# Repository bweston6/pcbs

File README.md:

# PCBs
## PiKVM
The [PiPVM](https://github.com/pikvm/pikvm) project requires some additional hardware for ATX system control.

This PCB implements the circuit from this section: <https://github.com/pikvm/pikvm#setting-up-the-v2> in a Raspberry Pi uHat footprint, per the specification at <https://github.com/raspberrypi/hats>.

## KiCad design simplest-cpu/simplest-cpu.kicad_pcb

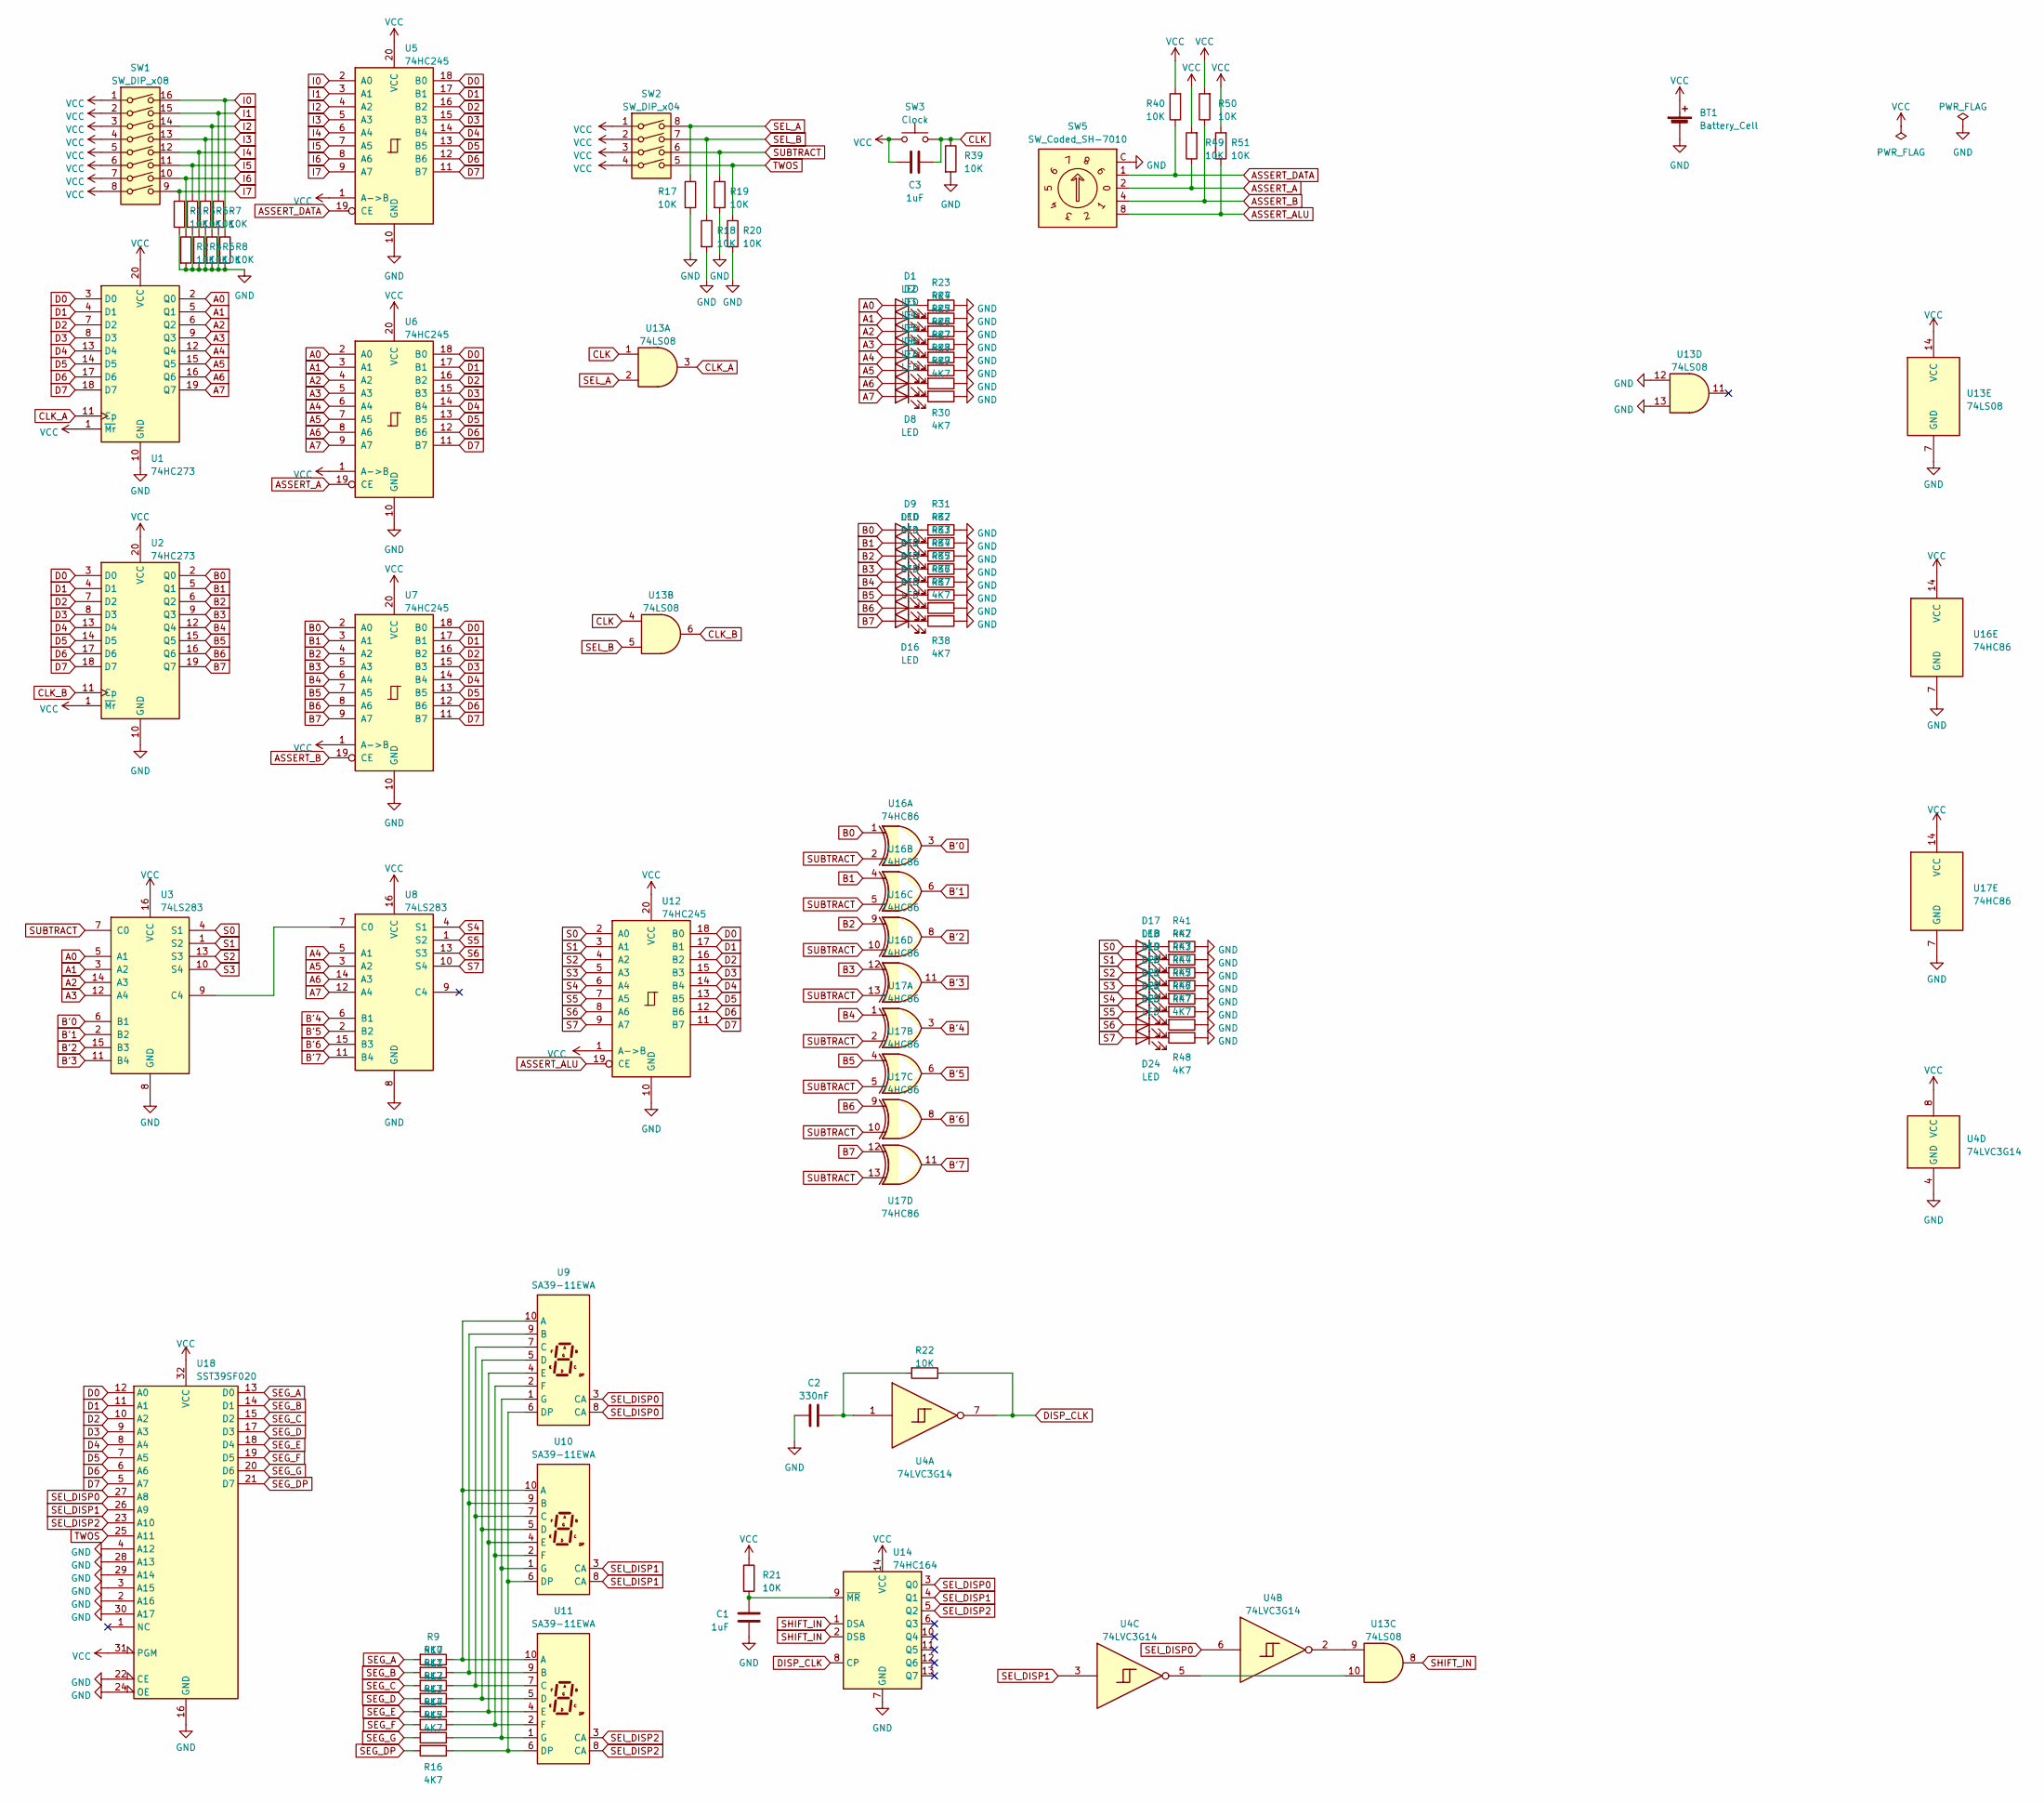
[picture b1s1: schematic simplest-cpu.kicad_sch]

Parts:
BT1: Battery_Cell; BatteryHolder_Keystone_3034_1x20mm
C1, C3: 1uF; C_0805_2012Metric_Pad1.18x1.45mm_HandSolder
C2: 330nF; C_0805_2012Metric_Pad1.18x1.45mm_HandSolder
D1, D2, D3, D4, D5, D6, D7, D8, D9, D10, D11, D12, D13, D14, D15, D16, D17, D18, D19, D20, D21, D22, D23, D24: LED; LED_0805_2012Metric_Pad1.15x1.40mm_HandSolder
R1, R2, R3, R4, R5, R6, R7, R8, R17, R18, R19, R20, R21, R22, R39, R40, R49, R50, R51: 10K; R_0805_2012Metric_Pad1.20x1.40mm_HandSolder
R9, R10, R11, R12, R13, R14, R15, R16, R23, R24, R25, R26, R27, R28, R29, R30, R31, R32, R33, R34, R35, R36, R37, R38, R41, R42, R43, R44, R45, R46, R47, R48: 4K7; R_0805_2012Metric_Pad1.20x1.40mm_HandSolder
SW1: SW_DIP_x08; SW_DIP_SPSTx08_Slide_6.7x21.88mm_W7.62mm_P2.54mm_LowProfile
SW2: SW_DIP_x04; SW_DIP_SPSTx04_Slide_6.7x11.72mm_W7.62mm_P2.54mm_LowProfile
SW3: Clock; SW_Cherry_MX_1.00u_PCB
SW5: SW_Coded_SH-7010; Nidec_Copal_SH-7010C
U1, U2: 74HC273; TSSOP-20_4.4x6.5mm_P0.65mm
U3, U8: 74LS283; DIP-16_W7.62mm
U4: 74LVC3G14; SSOP-8_2.95x2.8mm_P0.65mm
U5, U6, U7, U12: 74HC245; TSSOP-20_4.4x6.5mm_P0.65mm
U9, U10, U11: SA39-11EWA; Sx39-1xxxxx
U13: 74LS08; TSSOP-14_4.4x5mm_P0.65mm
U14: 74HC164; TSSOP-14_4.4x5mm_P0.65mm
U16, U17: 74HC86; TSSOP-14_4.4x5mm_P0.65mm
U18: SST39SF020; PLCC-32_THT-Socket

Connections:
A0: D1.2 (A), U1.2 (Q0), U3.5 (A1), U6.2 (A0)
A1: D2.2 (A), U1.5 (Q1), U3.3 (A2), U6.3 (A1)
A2: D3.2 (A), U1.6 (Q2), U3.14 (A3), U6.4 (A2)
A3: D4.2 (A), U1.9 (Q3), U3.12 (A4), U6.5 (A3)
A4: D5.2 (A), U1.12 (Q4), U6.6 (A4), U8.5 (A1)
A5: D6.2 (A), U1.15 (Q5), U6.7 (A5), U8.3 (A2)
A6: D7.2 (A), U1.16 (Q6), U6.8 (A6), U8.14 (A3)
A7: D8.2 (A), U1.19 (Q7), U6.9 (A7), U8.12 (A4)
ASSERT_A: R49.1, SW5.2, U6.19 (CE)
ASSERT_ALU: R51.1, SW5.8, U12.19 (CE)
ASSERT_B: R50.1, SW5.4, U7.19 (CE)
ASSERT_DATA: R40.1, SW5.1, U5.19 (CE)
B0: D9.2 (A), U2.2 (Q0), U7.2 (A0), U16.1
B1: D10.2 (A), U2.5 (Q1), U7.3 (A1), U16.4
B2: D11.2 (A), U2.6 (Q2), U7.4 (A2), U16.9
B3: D12.2 (A), U2.9 (Q3), U7.5 (A3), U16.12
B4: D13.2 (A), U2.12 (Q4), U7.6 (A4), U17.1
B5: D14.2 (A), U2.15 (Q5), U7.7 (A5), U17.4
B6: D15.2 (A), U2.16 (Q6), U7.8 (A6), U17.9
B7: D16.2 (A), U2.19 (Q7), U7.9 (A7), U17.12
B'0: U3.6 (B1), U16.3
B'1: U3.2 (B2), U16.6
B'2: U3.15 (B3), U16.8
B'3: U3.11 (B4), U16.11
B'4: U8.6 (B1), U17.3
B'5: U8.2 (B2), U17.6
B'6: U8.15 (B3), U17.8
B'7: U8.11 (B4), U17.11
CLK: C3.1, R39.1, SW3.2, U13.1, U13.4
CLK_A: U1.11 (Cp), U13.3
CLK_B: U2.11 (Cp), U13.6
D0: U1.3 (D0), U2.3 (D0), U5.18 (B0), U6.18 (B0), U7.18 (B0), U12.18 (B0), U18.12 (A0)
D1: U1.4 (D1), U2.4 (D1), U5.17 (B1), U6.17 (B1), U7.17 (B1), U12.17 (B1), U18.11 (A1)
D2: U1.7 (D2), U2.7 (D2), U5.16 (B2), U6.16 (B2), U7.16 (B2), U12.16 (B2), U18.10 (A2)
D3: U1.8 (D3), U2.8 (D3), U5.15 (B3), U6.15 (B3), U7.15 (B3), U12.15 (B3), U18.9 (A3)
D4: U1.13 (D4), U2.13 (D4), U5.14 (B4), U6.14 (B4), U7.14 (B4), U12.14 (B4), U18.8 (A4)
D5: U1.14 (D5), U2.14 (D5), U5.13 (B5), U6.13 (B5), U7.13 (B5), U12.13 (B5), U18.7 (A5)
D6: U1.17 (D6), U2.17 (D6), U5.12 (B6), U6.12 (B6), U7.12 (B6), U12.12 (B6), U18.6 (A6)
D7: U1.18 (D7), U2.18 (D7), U5.11 (B7), U6.11 (B7), U7.11 (B7), U12.11 (B7), U18.5 (A7)
DISP_CLK: R22.1, U4.7, U14.8 (CP)
GND: BT1.2 (-), C1.1, C2.1, R1.2, R2.2, R3.2, R4.2, R5.2, R6.2, R7.2, R8.2, R17.2, R18.2, R19.2, R20.2, R23.1, R24.1, R25.1, R26.1, R27.1, R28.1, R29.1, R30.1, R31.1, R32.1, R33.1, R34.1, R35.1, R36.1, R37.1, R38.1, R39.2, R41.1, R42.1, R43.1, R44.1, R45.1, R46.1, R47.1, R48.1, SW5.C, U1.10 (GND), U2.10 (GND), U3.8 (GND), U4.4 (GND), U5.10 (GND), U6.10 (GND), U7.10 (GND), U8.8 (GND), U12.10 (GND), U13.7 (GND), U13.12, U13.13, U14.7 (GND), U16.7 (GND), U17.7 (GND), U18.2 (A16), U18.3 (A15), U18.4 (A12), U18.16 (GND), U18.22 (CE), U18.24 (OE), U18.28 (A13), U18.29 (A14), U18.30 (A17)
I0: R8.1, SW1.16, U5.2 (A0)
I1: R7.1, SW1.15, U5.3 (A1)
I2: R6.1, SW1.14, U5.4 (A2)
I3: R5.1, SW1.13, U5.5 (A3)
I4: R4.1, SW1.12, U5.6 (A4)
I5: R3.1, SW1.11, U5.7 (A5)
I6: R2.1, SW1.10, U5.8 (A6)
I7: R1.1, SW1.9, U5.9 (A7)
unnamed: C2.2, R22.2, U4.1
unnamed: D1.1 (K), R23.2
unnamed: D2.1 (K), R24.2
unnamed: D3.1 (K), R25.2
unnamed: D4.1 (K), R26.2
unnamed: D5.1 (K), R27.2
unnamed: D6.1 (K), R28.2
unnamed: D7.1 (K), R29.2
unnamed: D8.1 (K), R30.2
unnamed: D9.1 (K), R31.2
unnamed: D10.1 (K), R32.2
unnamed: D11.1 (K), R33.2
unnamed: D12.1 (K), R34.2
unnamed: D13.1 (K), R35.2
unnamed: D14.1 (K), R36.2
unnamed: D15.1 (K), R37.2
unnamed: D16.1 (K), R38.2
unnamed: D17.1 (K), R41.2
unnamed: D18.1 (K), R42.2
unnamed: D19.1 (K), R43.2
unnamed: D20.1 (K), R44.2
unnamed: D21.1 (K), R45.2
unnamed: D22.1 (K), R46.2
unnamed: D23.1 (K), R47.2
unnamed: D24.1 (K), R48.2
unnamed: U3.9 (C4), U8.7 (C0)
unnamed: R9.1, U9.10 (A), U10.10 (A), U11.10 (A)
unnamed: R10.1, U9.9 (B), U10.9 (B), U11.9 (B)
unnamed: R11.1, U9.7 (C), U10.7 (C), U11.7 (C)
unnamed: R12.1, U9.5 (D), U10.5 (D), U11.5 (D)
unnamed: R16.1, U9.6 (DP), U10.6 (DP), U11.6 (DP)
unnamed: R13.1, U9.4 (E), U10.4 (E), U11.4 (E)
unnamed: R14.1, U9.2 (F), U10.2 (F), U11.2 (F)
unnamed: R15.1, U9.1 (G), U10.1 (G), U11.1 (G)
unnamed: U4.2, U13.9
unnamed: U4.5, U13.10
unnamed: C1.2, R21.2, U14.9 (~MR)
S0: D17.2 (A), U3.4 (S1), U12.2 (A0)
S1: D18.2 (A), U3.1 (S2), U12.3 (A1)
S2: D19.2 (A), U3.13 (S3), U12.4 (A2)
S3: D20.2 (A), U3.10 (S4), U12.5 (A3)
S4: D21.2 (A), U8.4 (S1), U12.6 (A4)
S5: D22.2 (A), U8.1 (S2), U12.7 (A5)
S6: D23.2 (A), U8.13 (S3), U12.8 (A6)
S7: D24.2 (A), U8.10 (S4), U12.9 (A7)
SEG_A: R9.2, U18.13 (D0)
SEG_B: R10.2, U18.14 (D1)
SEG_C: R11.2, U18.15 (D2)
SEG_D: R12.2, U18.17 (D3)
SEG_DP: R16.2, U18.21 (D7)
SEG_E: R13.2, U18.18 (D4)
SEG_F: R14.2, U18.19 (D5)
SEG_G: R15.2, U18.20 (D6)
SEL_A: R17.1, SW2.8, U13.2
SEL_B: R18.1, SW2.7, U13.5
SEl_DISP0: U4.6, U9.3 (CA), U9.8 (CA), U14.3 (Q0), U18.27 (A8)
SEl_DISP1: U4.3, U10.3 (CA), U10.8 (CA), U14.4 (Q1), U18.26 (A9)
SEl_DISP2: U11.3 (CA), U11.8 (CA), U14.5 (Q2), U18.23 (A10)
SHIFT_IN: U13.8, U14.1 (DSA), U14.2 (DSB)
SUBTRACT: R19.1, SW2.6, U3.7 (C0), U16.2, U16.5, U16.10, U16.13, U17.2, U17.5, U17.10, U17.13
TWOS: R20.1, SW2.5, U18.25 (A11)
VCC: BT1.1 (+), C3.2, R21.1, R40.2, R49.2, R50.2, R51.2, SW1.1, SW1.2, SW1.3, SW1.4, SW1.5, SW1.6, SW1.7, SW1.8, SW2.1, SW2.2, SW2.3, SW2.4, SW3.1, U1.1 (~Mr), U1.20 (VCC), U2.1 (~Mr), U2.20 (VCC), U3.16 (VCC), U4.8 (VCC), U5.1 (A->B), U5.20 (VCC), U6.1 (A->B), U6.20 (VCC), U7.1 (A->B), U7.20 (VCC), U8.16 (VCC), U12.1 (A->B), U12.20 (VCC), U13.14 (VCC), U14.14 (VCC), U16.14 (VCC), U17.14 (VCC), U18.31 (PGM), U18.32 (VCC)

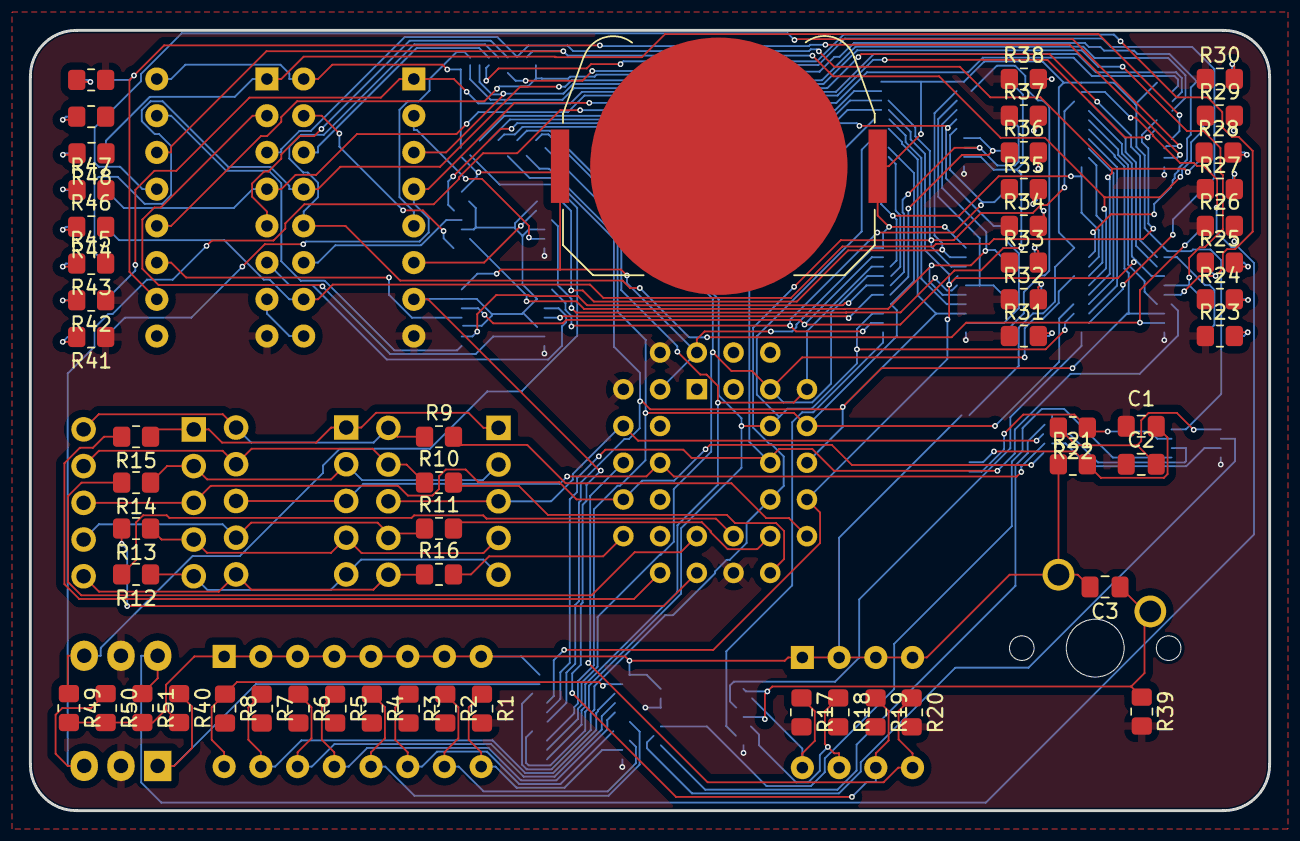
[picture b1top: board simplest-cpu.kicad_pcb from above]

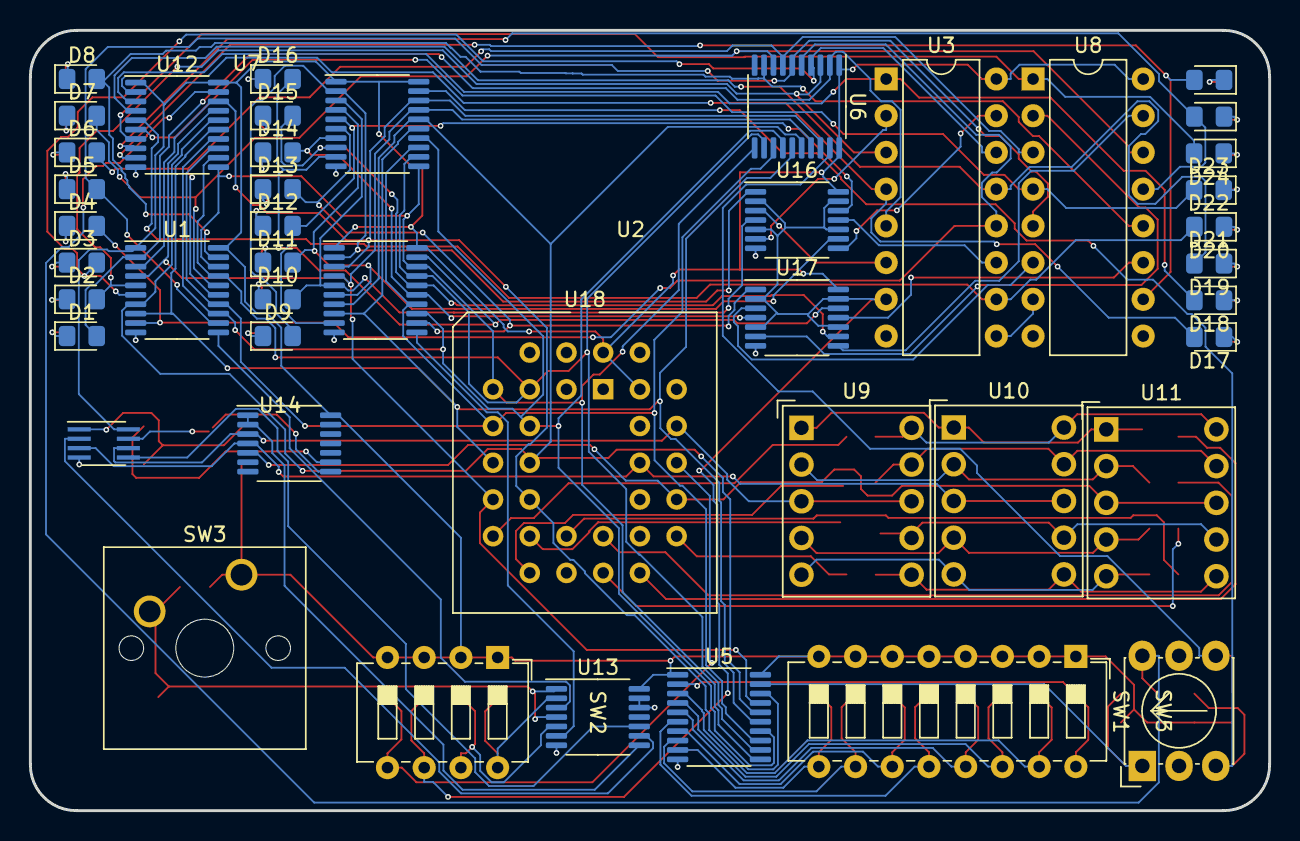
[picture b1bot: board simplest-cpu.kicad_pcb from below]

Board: 2 copper layers, 85.7 x 54.0 mm, 100 parts (45 on the bottom side), 111 nets.

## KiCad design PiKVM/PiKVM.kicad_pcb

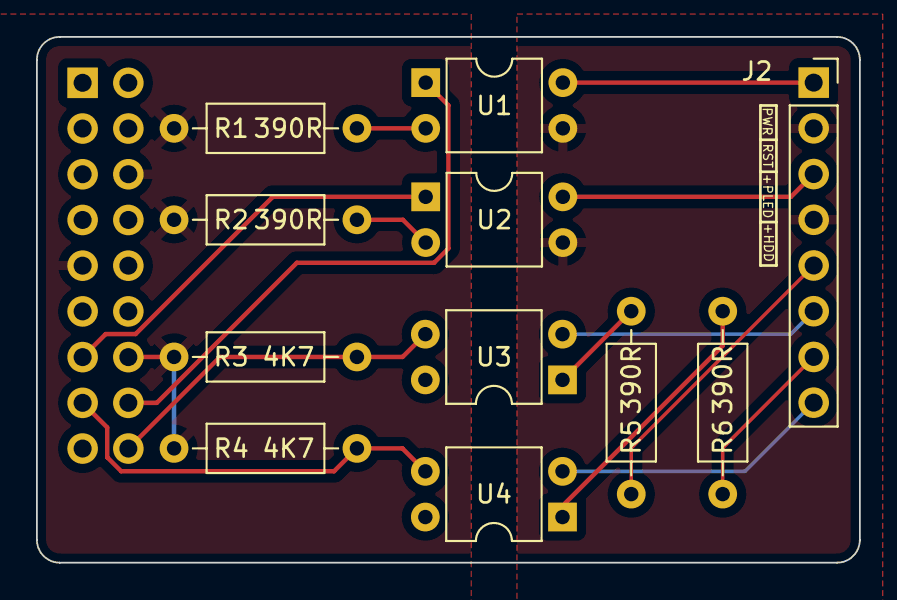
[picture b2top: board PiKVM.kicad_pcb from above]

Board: 2 copper layers, 45.7 x 29.2 mm, 12 parts (1 on the bottom side), 17 nets.

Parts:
J1: Raspberry_Pi_2_3; PinSocket_2x09_P2.54mm_Vertical
J2: Conn_01x08; PinSocket_1x08_P2.54mm_Vertical
R1, R2, R5, R6: 390R; R_Axial_DIN0207_L6.3mm_D2.5mm_P10.16mm_Horizontal
R3, R4: 4K7; R_Axial_DIN0207_L6.3mm_D2.5mm_P10.16mm_Horizontal
U1, U2, U3, U4: TLP222A; DIP-4_W7.62mm

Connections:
+3V3: J1.1 (3V3), J1.17 (3V3), U3.4, U4.4
GND1: J1.6 (GND), J1.9 (GND), J1.14 (GND), R1.1, R2.1, R3.1, R4.1
GND2: J2.2, J2.4, U1.3, U2.3
IDLE_LED: J1.15 (GPIO22), R4.2, U4.3
IDLE_LED+: J2.7, R6.2
IDLE_LED-: J2.8, U4.2
unnamed: R1.2, U1.2
unnamed: R2.2, U2.2
unnamed: R5.1, U3.1
unnamed: R6.1, U4.1
PLED: J1.18 (GPIO24), R3.2, U3.3
PLED+: J2.5, R5.2
PLED-: J2.6, U3.2
PWR+: J2.1, U1.4
PWRSW: J1.16 (GPIO23), U1.1
RST+: J2.3, U2.4
RSTSW: J1.13 (GPIO27), U2.1

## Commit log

2022-11-05 Initial commit.
2022-11-05 Add readme
2022-11-05 Update image link
2023-03-13 Updating file version.
2023-03-13 Initial commit for super simple CPU.
